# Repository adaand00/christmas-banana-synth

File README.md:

# Christmas banana synth - Christmas card for 2022

The Christmas banana synth is a stylophone synthesizer with 24 keys and a buzzer for sound. The back features PCB art of a winter landscape. There are also 12 built-in songs available. We used assembly of components by JLCPCB to speed up the process, since we made around 25 boards.

## Video sample (Turn on sound)

https://github.com/adaand00/christmas-banana-synth/assets/45564940/3717fd15-4f71-4382-aa24-0abd6eaa9e98

Credit to Johan (@johanwheeler) for the playing.

## Images

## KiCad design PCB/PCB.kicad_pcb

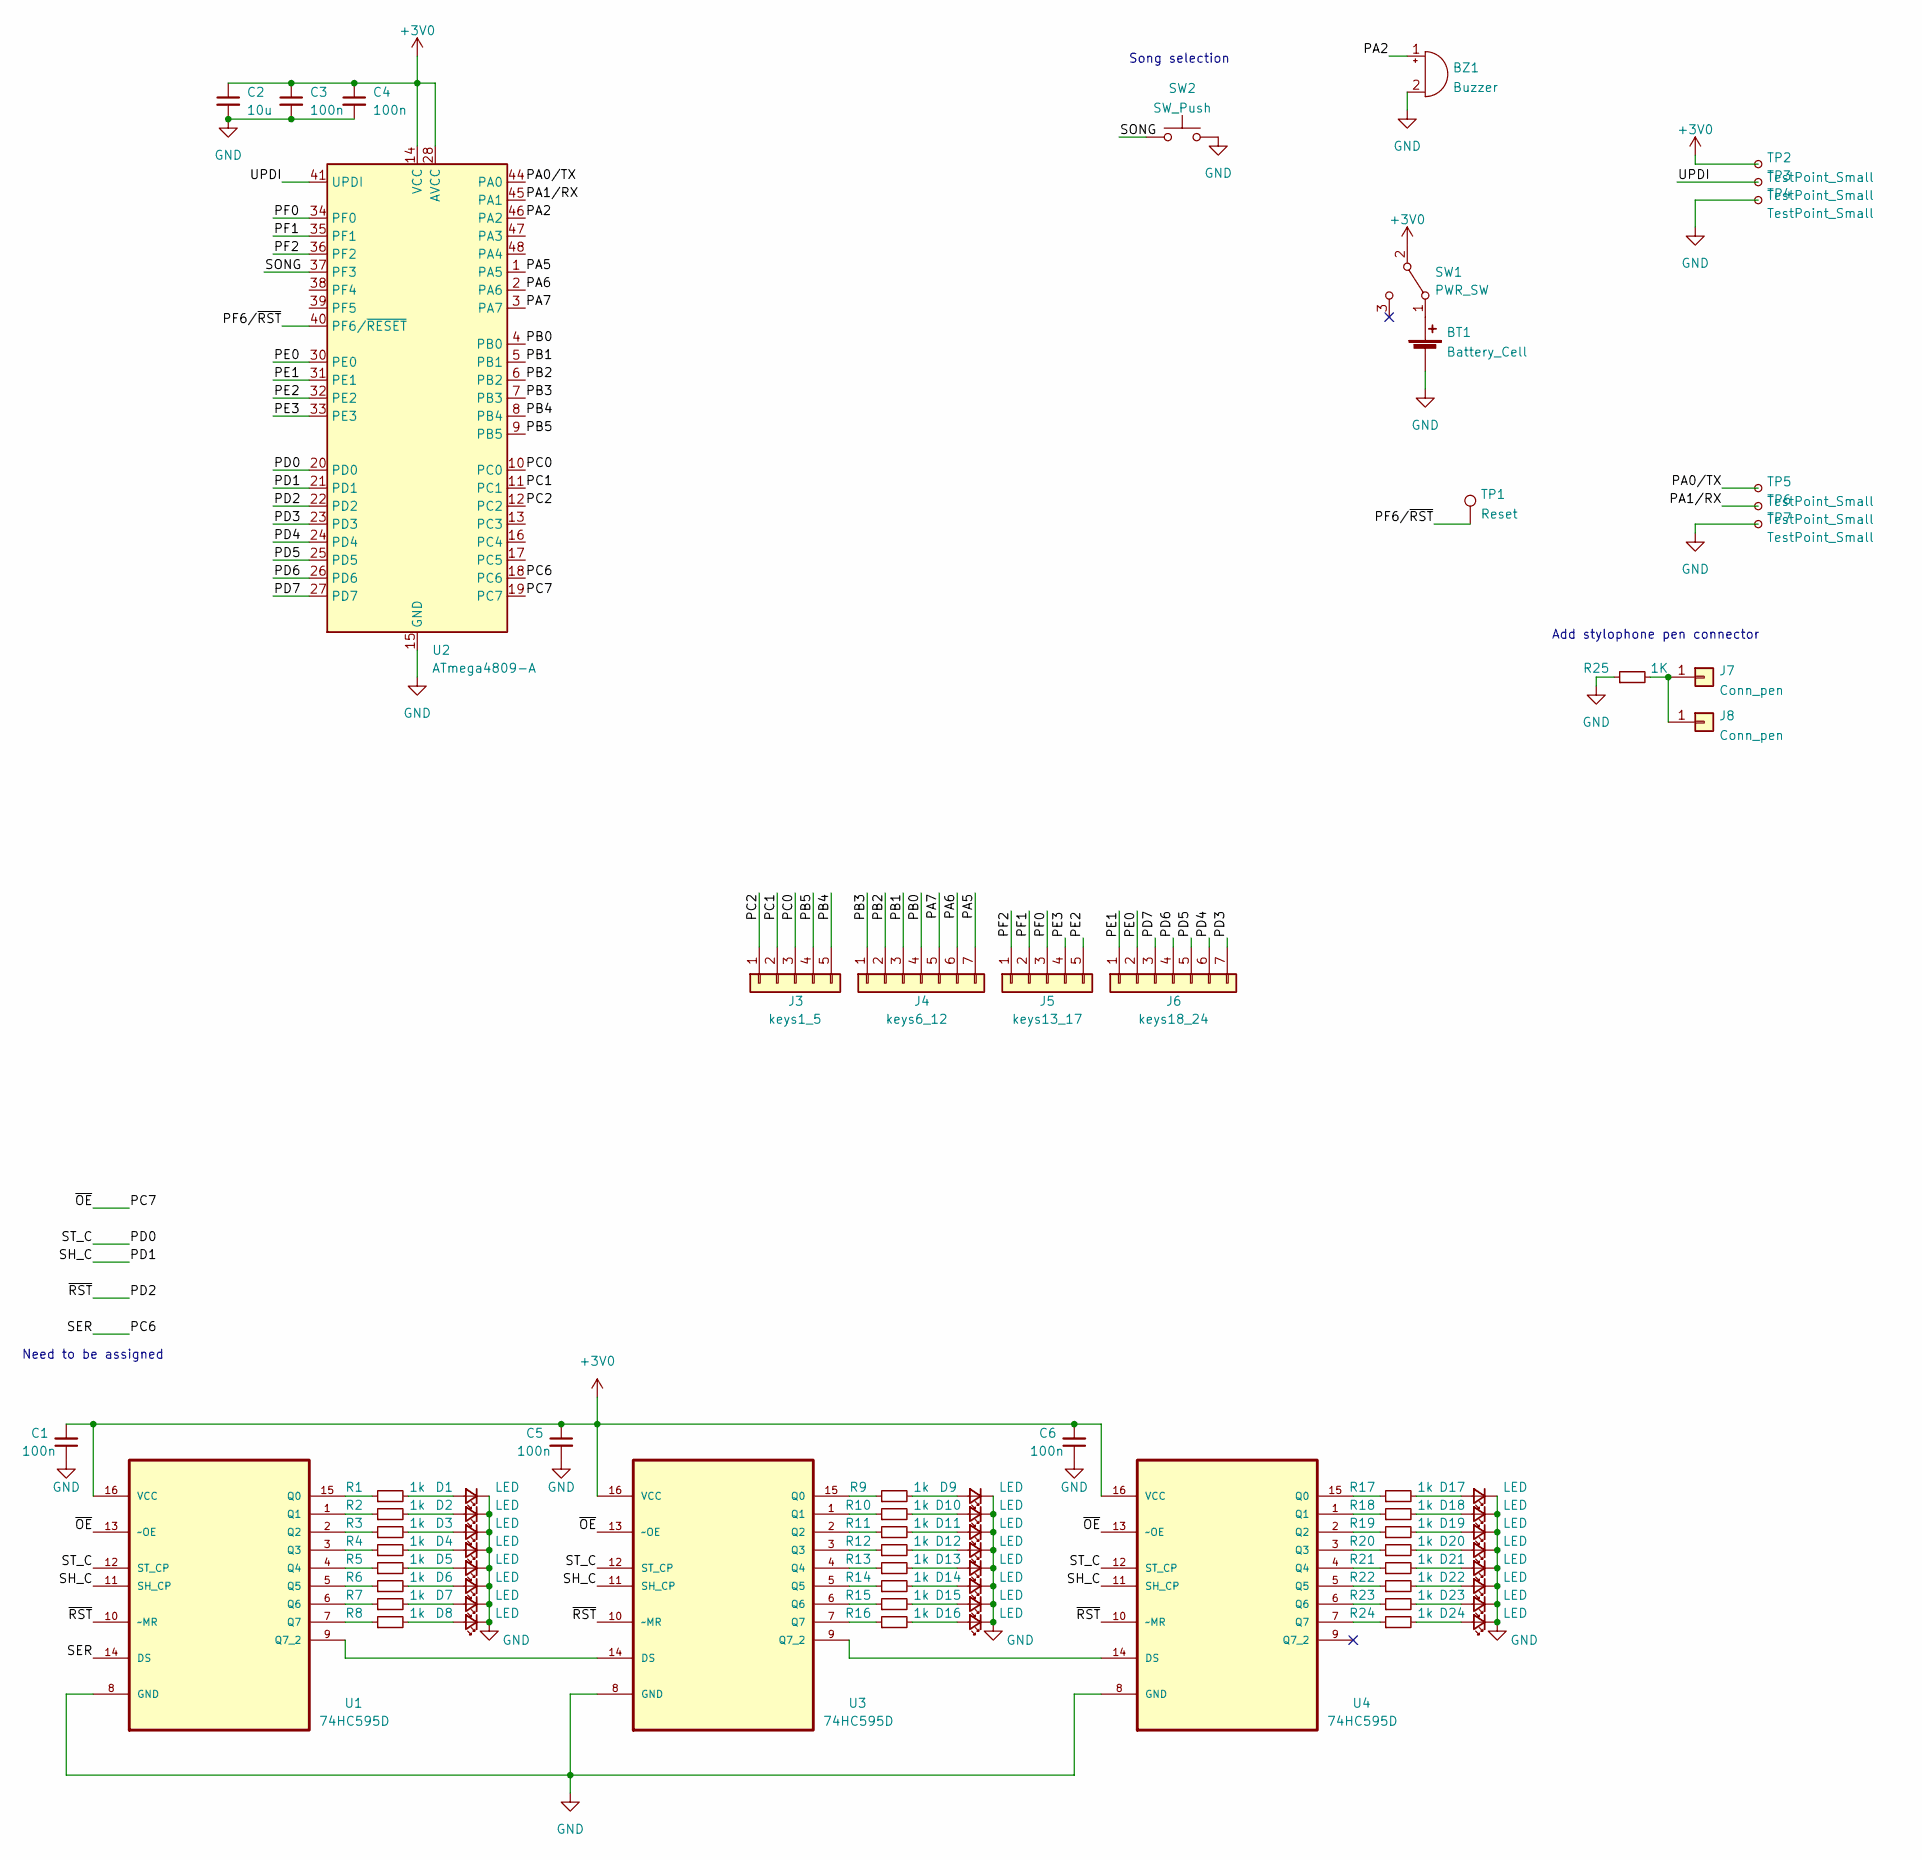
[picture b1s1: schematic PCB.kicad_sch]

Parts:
BT1: Battery_Cell; BAT-HLD-001
BZ1: Buzzer; CPT-1117-BUZZ
C1, C3, C4, C5, C6: 100n; C_0603_1608Metric
C2: 10u; C_0603_1608Metric
D1, D2, D3, D4, D5, D6, D7, D8, D9, D10, D11, D12, D13, D14, D15, D16, D17, D18, D19, D20, D21, D22, D23, D24: LED; LED_0603_1608Metric
J3: keys1_5; 3w2bv2
J4: keys6_12; 4w3bv2
J5: keys13_17; 3w2bv2
J6: keys18_24; 4w3bv2
J7, J8: Conn_pen; MountingHole_2.2mm_M2_Pad_Via
R1, R2, R3, R4, R5, R6, R7, R8, R9, R10, R11, R12, R13, R14, R15, R16, R17, R18, R19, R20, R21, R22, R23, R24: 1k; R_0603_1608Metric
R25: 1K; R_0603_1608Metric
SW1: PWR_SW; SW_SPDT_CK-JS102011SAQN
SW2: SW_Push; SW_Push_1P1T_NO_CK_KSC6xxJ
TP1: Reset; TestPoint_Pad_D2.0mm
TP2, TP3, TP4, TP5, TP6, TP7: TestPoint_Small; TestPoint_Pad_D1.5mm
U1, U3, U4: 74HC595D; SOIC127P600X175-16N; MPN 74HC595D,118
U2: ATmega4809-A; TQFP-48_7x7mm_P0.5mm

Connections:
+3V0: C1.2, C2.1, C3.1, C4.1, C5.1, C6.2, SW1.2 (B), TP2.1, U1.16 (VCC), U2.14 (VCC), U2.28 (AVCC), U2.42 (VCC), U3.16 (VCC), U4.16 (VCC)
/PA0/TX: TP5.1, U2.44 (PA0)
/PA1/RX: TP6.1, U2.45 (PA1)
/PA2: BZ1.1 (-), U2.46 (PA2)
/PA5: J4.7, U2.1 (PA5)
/PA6: J4.6, U2.2 (PA6)
/PA7: J4.5, U2.3 (PA7)
/PB0: J4.4, U2.4 (PB0)
/PB1: J4.3, U2.5 (PB1)
/PB2: J4.2, U2.6 (PB2)
/PB3: J4.1, U2.7 (PB3)
/PB4: J3.5, U2.8 (PB4)
/PB5: J3.4, U2.9 (PB5)
/PC0: J3.3, U2.10 (PC0)
/PC1: J3.2, U2.11 (PC1)
/PC2: J3.1, U2.12 (PC2)
/PC6: U1.14 (DS), U2.18 (PC6)
/PC7: U1.13 (~OE), U2.19 (PC7), U3.13 (~OE), U4.13 (~OE)
/PD0: U1.12 (ST_CP), U2.20 (PD0), U3.12 (ST_CP), U4.12 (ST_CP)
/PD1: U1.11 (SH_CP), U2.21 (PD1), U3.11 (SH_CP), U4.11 (SH_CP)
/PD2: U1.10 (~MR), U2.22 (PD2), U3.10 (~MR), U4.10 (~MR)
/PD3: J6.7, U2.23 (PD3)
/PD4: J6.6, U2.24 (PD4)
/PD5: J6.5, U2.25 (PD5)
/PD6: J6.4, U2.26 (PD6)
/PD7: J6.3, U2.27 (PD7)
/PE0: J6.2, U2.30 (PE0)
/PE1: J6.1, U2.31 (PE1)
/PE2: J5.5, U2.32 (PE2)
/PE3: J5.4, U2.33 (PE3)
/PF0: J5.3, U2.34 (PF0)
/PF1: J5.2, U2.35 (PF1)
/PF2: J5.1, U2.36 (PF2)
/PF6/~RST: TP1.1, U2.40 (PF6/~RESET)
/SONG: SW2.1, U2.37 (PF3)
/UPDI: TP3.1, U2.41 (UPDI)
GND: BT1.2 (-), BZ1.2 (+), C1.1, C2.2, C3.2, C4.2, C5.2, C6.1, D1.1 (K), D2.1 (K), D3.1 (K), D4.1 (K), D5.1 (K), D6.1 (K), D7.1 (K), D8.1 (K), D9.1 (K), D10.1 (K), D11.1 (K), D12.1 (K), D13.1 (K), D14.1 (K), D15.1 (K), D16.1 (K), D17.1 (K), D18.1 (K), D19.1 (K), D20.1 (K), D21.1 (K), D22.1 (K), D23.1 (K), D24.1 (K), R25.1, SW2.2, TP4.1, TP7.1, U1.8 (GND), U2.15 (GND), U2.29 (GND), U2.43 (GND), U3.8 (GND), U4.8 (GND)
unnamed: BT1.1 (+), SW1.1 (A)
unnamed: D1.2 (A), R1.2
unnamed: D2.2 (A), R2.2
unnamed: D3.2 (A), R3.2
unnamed: D4.2 (A), R4.2
unnamed: D5.2 (A), R5.2
unnamed: D6.2 (A), R6.2
unnamed: D7.2 (A), R7.2
unnamed: D8.2 (A), R8.2
unnamed: D9.2 (A), R9.2
unnamed: D10.2 (A), R10.2
unnamed: D11.2 (A), R11.2
unnamed: D12.2 (A), R12.2
unnamed: D13.2 (A), R13.2
unnamed: D14.2 (A), R14.2
unnamed: D15.2 (A), R15.2
unnamed: D16.2 (A), R16.2
unnamed: D17.2 (A), R17.2
unnamed: D18.2 (A), R18.2
unnamed: D19.2 (A), R19.2
unnamed: D20.2 (A), R20.2
unnamed: D21.2 (A), R21.2
unnamed: D22.2 (A), R22.2
unnamed: D23.2 (A), R23.2
unnamed: D24.2 (A), R24.2
unnamed: J7.1, J8.1, R25.2
unnamed: R1.1, U1.15 (Q0)
unnamed: R2.1, U1.1 (Q1)
unnamed: R3.1, U1.2 (Q2)
unnamed: R4.1, U1.3 (Q3)
unnamed: R5.1, U1.4 (Q4)
unnamed: R6.1, U1.5 (Q5)
unnamed: R7.1, U1.6 (Q6)
unnamed: R8.1, U1.7 (Q7)
unnamed: R9.1, U3.15 (Q0)
unnamed: R10.1, U3.1 (Q1)
unnamed: R11.1, U3.2 (Q2)
unnamed: R12.1, U3.3 (Q3)
unnamed: R13.1, U3.4 (Q4)
unnamed: R14.1, U3.5 (Q5)
unnamed: R15.1, U3.6 (Q6)
unnamed: R16.1, U3.7 (Q7)
unnamed: R17.1, U4.15 (Q0)
unnamed: R18.1, U4.1 (Q1)
unnamed: R19.1, U4.2 (Q2)
unnamed: R20.1, U4.3 (Q3)
unnamed: R21.1, U4.4 (Q4)
unnamed: R22.1, U4.5 (Q5)
unnamed: R23.1, U4.6 (Q6)
unnamed: R24.1, U4.7 (Q7)
unnamed: U1.9 (Q7_2), U3.14 (DS)
unnamed: U3.9 (Q7_2), U4.14 (DS)

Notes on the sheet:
Song selection
Need to be assigned
Add stylophone pen connector

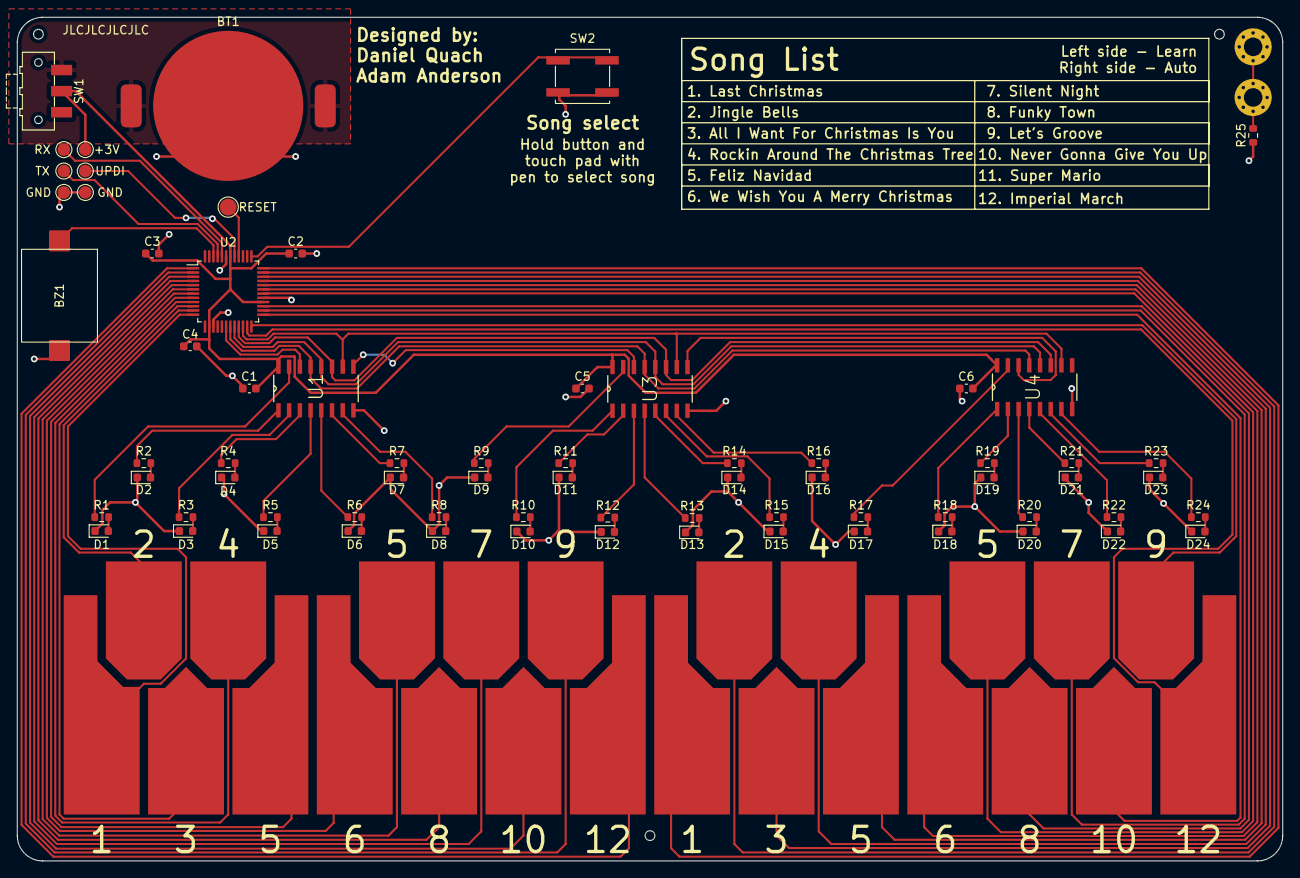
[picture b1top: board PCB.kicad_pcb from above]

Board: 2 copper layers, 150.0 x 100.0 mm, 77 parts (1 on the bottom side), 89 nets.

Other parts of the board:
Ref**: Val**; Vectorized

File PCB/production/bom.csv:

Designator,Footprint,Quantity,Value,LCSC Part #
"C1, C3, C4, C5, C6",C_0603_1608Metric,5,100n,C14663
C2,C_0603_1608Metric,1,10u,C19702
"D1, D10, D11, D12, D13, D14, D15, D16, D17, D18, D19, D2, D20, D21, D22, D23, D24, D3, D4, D5, D6, D7, D8, D9",LED_0603_1608Metric,24,LED,C72043
"R1, R10, R11, R12, R13, R14, R15, R16, R17, R18, R19, R2, R20, R21, R22, R23, R24, R25, R3, R4, R5, R6, R7, R8, R9",R_0603_1608Metric,25,1k,C21190
SW2,SW_Push_1P1T_NO_CK_KSC6xxJ,1,SW_Push,C318884
"U1, U3, U4",SOIC127P600X175-16N,3,74HC595D,C5947

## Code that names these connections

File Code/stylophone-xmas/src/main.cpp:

#include <Arduino.h>
#include "songs.h"

int keys[] = {
  PIN_PC2, PIN_PC1, PIN_PC0, PIN_PB5, PIN_PB4,
  PIN_PB3, PIN_PB2, PIN_PB1, PIN_PB0, PIN_PA7, PIN_PA6, PIN_PA5,
  PIN_PF2, PIN_PF1, PIN_PF0, PIN_PE3, PIN_PE2,
  PIN_PE1, PIN_PE0, PIN_PD7, PIN_PD6, PIN_PD5, PIN_PD4, PIN_PD3
};

// frequencies from C4 to B5
unsigned int freqz[] = {
  261, 277, 293, 311, 329, 349, 369, 391, 415, 440, 466, 493,
  523, 554, 587, 622, 659, 698, 739, 783, 830, 880, 932, 987
};

uint32_t waitTime = 0;

#define KEY_COUNT 24
#define BUZZER_PIN PIN_PA2
#define BUTTON_PIN PIN_PF3

#define OE_PIN PIN_PC7
#define STORAGE_CLOCK_PIN PIN_PD0
#define SHIFT_CLOCK_PIN PIN_PD1
#define SHIFT_NRST_PIN PIN_PD2
#define DATA_PIN PIN_PC6

void shift_clock() {
  digitalWrite(SHIFT_CLOCK_PIN,   HIGH);
  //digitalWrite probably has enough delay to clock correctly 
  digitalWrite(SHIFT_CLOCK_PIN,   LOW);
}

void LED_show() {
  digitalWrite(STORAGE_CLOCK_PIN, LOW);
  digitalWrite(STORAGE_CLOCK_PIN, HIGH);
}

void LED_clear() {
  digitalWrite(SHIFT_NRST_PIN, LOW);
  digitalWrite(SHIFT_NRST_PIN, HIGH);

  LED_show();
}

void LED_on(int key) {
  LED_clear();
  digitalWrite(DATA_PIN, HIGH);
  shift_clock();
  digitalWrite(DATA_PIN, LOW);

  for (int i = 0; i < key; i++) {
    shift_clock();
  }

  LED_show();
}

int readKeys(){
  for (int i = 0; i < KEY_COUNT; i++) {
    if (digitalRead(keys[i]) == LOW) {
      return i;
    }
  }
  return -1;
}

void playSong(const note_t * song, int length){

  for (int i = 0; i < length; i++) {
    if (song[i].note == 0) {
      noTone(BUZZER_PIN);
      LED_clear();
      delay(song[i].duration);
      continue;
    }

    uint8_t note = song[i].note-1;

    tone(BUZZER_PIN, freqz[note]);
    LED_on(note);
    delay(song[i].duration);
  }

  noTone(BUZZER_PIN);
}

void learnSong(const note_t * song, int length){

  // start learning mode
  for (int i = 0; i < length; i++) {
    if(song[i].note == 0){
      noTone(BUZZER_PIN);
      LED_clear();
      delay(song[i].duration);
      continue;
    }

    uint8_t note = song[i].note-1;

    // turn on LED
    LED_on(note);

    // wait for note to be played
    while (readKeys() != note) { delay(10); }

    //start LED timer
    unsigned long start = millis();

    // wait for duration note to end
    while (millis() - start < song[i].duration)
    {

      if (readKeys() == note) {
        tone(BUZZER_PIN, freqz[note]);
      }else{
        noTone(BUZZER_PIN);
      }

      delay(10);
    }

    LED_clear();

    // wait for note to be released
    while (readKeys() == note) { delay(10); }

    noTone(BUZZER_PIN);

  }
}


void setup() {
  // init keys as input with pullup
  for (int i = 0; i < KEY_COUNT; i++) {
    pinMode(keys[i], INPUT_PULLUP);
  }

  // init buzzer as output
  pinMode(BUZZER_PIN, OUTPUT);

  // init button as input with pullup
  pinMode(BUTTON_PIN, INPUT_PULLUP);

  // init shift register pins as output
  pinMode(OE_PIN, OUTPUT);
  pinMode(STORAGE_CLOCK_PIN, OUTPUT);
  pinMode(SHIFT_CLOCK_PIN, OUTPUT);
  pinMode(SHIFT_NRST_PIN, OUTPUT);
  pinMode(DATA_PIN, OUTPUT);

  // init shift registers
  digitalWrite(STORAGE_CLOCK_PIN, LOW);
  digitalWrite(SHIFT_CLOCK_PIN, LOW);
  LED_clear();
  digitalWrite(OE_PIN, LOW);

  // test all leds and buzzer
  for (int i = 0; i < KEY_COUNT; i++) {
    LED_on(i);
    tone(BUZZER_PIN, freqz[i]);
    delay(60);
  }

  //test buzzer
  tone(BUZZER_PIN, 440, 1000);

}

void loop() {
  // put your main code here, to run repeatedly:

  int key = readKeys();
  int songButton = digitalRead(BUTTON_PIN);

  if (key != -1 && songButton == LOW) {
    if(key<12)
      learnSong(songs[key], song_lengths[key]);
    else
      playSong(songs[key-12], song_lengths[key-12]);

    waitTime = 0;

  } else if (key != -1) {
    LED_on(key);
    tone(BUZZER_PIN, freqz[key]);
    waitTime = 0;
  } else {
    LED_clear();
    noTone(BUZZER_PIN);
  }

  // play snippet of song after 30 seconds
  waitTime += 10;
  if (waitTime > 30000) {
    playSong(songs[4], 10);
    waitTime = 0;
  }

  delay(10);
}

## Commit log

2022-11-19 Start on schematic
2022-11-19 Resize image
2022-11-19 schematic almost done
2022-11-20 added piano key footprints
2022-11-20 Rough placement of components done
2022-11-20 Start routing
2022-11-21 Routing of LEDS
2022-11-22 Routing, pin assignments
2022-11-24 Final routing
2022-11-24 Silkscreen
2022-11-24 JLC exports
2022-11-24 Gerbs
2022-11-25 Finishing touches
2022-11-25 Finishing touches 2
2022-11-25 V1.0
2022-12-01 Start code
2022-12-07 Fix for hardware
2022-12-07 Song structure started
2022-12-12 added midi test script
2022-12-12 Format as C 2D array
2022-12-12 Learning mode working, also inactivity timer
2022-12-13 More songs, speed tweak
2022-12-13 Added even more songs
2022-12-14 added silent night
2022-12-16 Songs and code for v1.0
2023-10-19 Add images and video
